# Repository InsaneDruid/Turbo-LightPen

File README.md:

# Turbo-LightPen
A 100% compatible replica of the Turbo Light Pen originally made for the C64. Can also work on the *High Speed Graphik* addon for the CBM PET line.

[Schematic](https://github.com/InsaneDruid/Turbo-LightPen/blob/main/Turbo-LightPen.pdf "Schematic")  

[Bill of Materials](https://htmlpreview.github.io/?https://github.com/InsaneDruid/Turbo-LightPen/blob/main/bom/Turbo-LightPen_bom.html "Bill of Materials")

## The License
This work is licensed under a Creative Commons Attribution-ShareAlike 4.0 International License.  
See https://creativecommons.org/licenses/by-sa/4.0/.

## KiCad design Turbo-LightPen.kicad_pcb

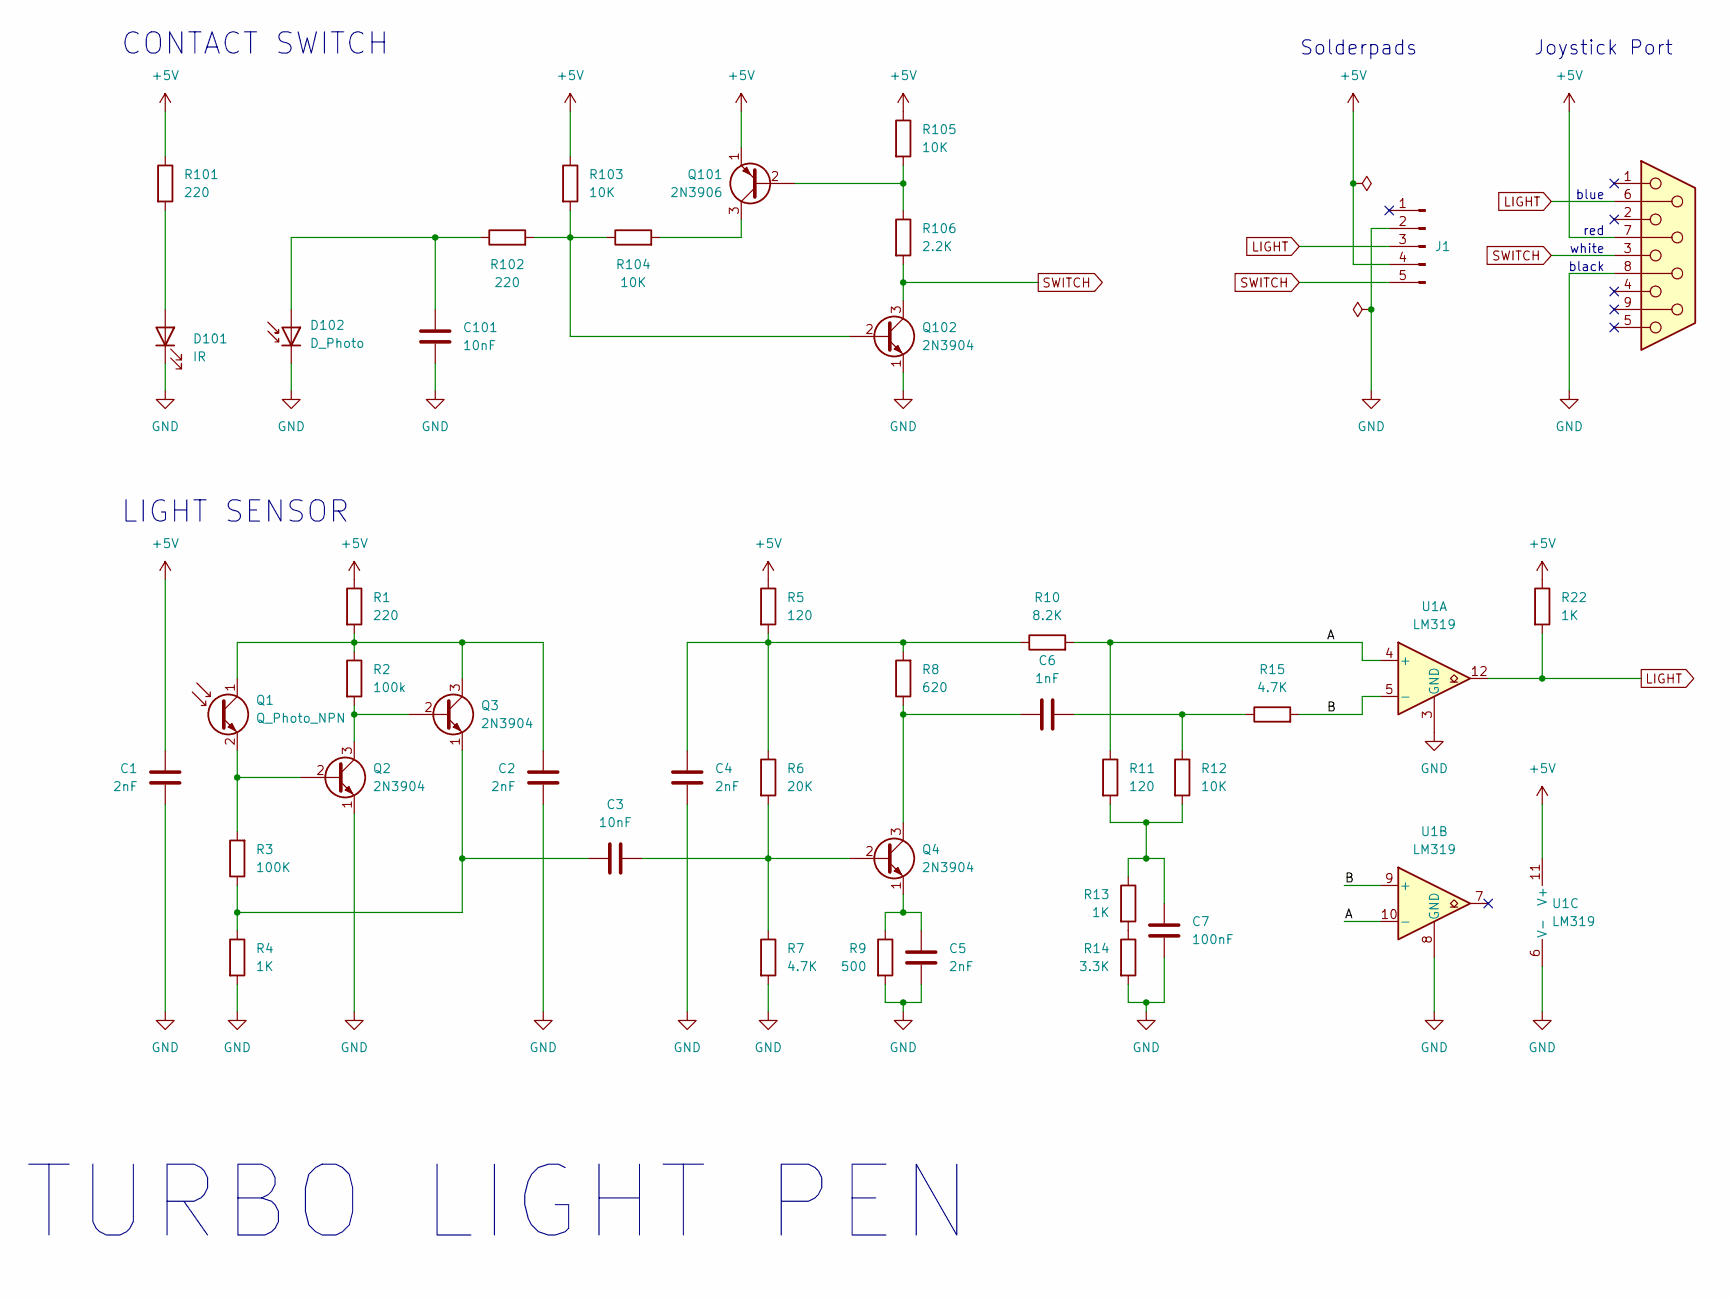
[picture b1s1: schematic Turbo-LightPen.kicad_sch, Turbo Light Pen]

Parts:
C1, C2, C4, C5: 2nF; C_Disc_D3.0mm_W1.6mm_P2.50mm
C3, C101: 10nF; C_Disc_D3.0mm_W1.6mm_P2.50mm
C6: 1nF; C_Disc_D3.0mm_W1.6mm_P2.50mm
C7: 100nF; C_Disc_D3.0mm_W1.6mm_P2.50mm
D101: IR; LED_Rectangular_W3.0mm_H2.0mm
D102: D_Photo; LED_Rectangular_W3.0mm_H2.0mm
J1: Conn_01x05_Pin; Cablepad_01x05
J2: Joystick Cable
Q1: Q_Photo_NPN; LED_D5.0mm_Horizontal_O6.35mm_Z3.0mm
Q2, Q3, Q4, Q102: 2N3904; TO-92_Inline
Q101: 2N3906; TO-92_Inline
R1, R101, R102: 220; R_Axial_DIN0204_L3.6mm_D1.6mm_P7.62mm_Horizontal
R2: 100k; R_Axial_DIN0204_L3.6mm_D1.6mm_P7.62mm_Horizontal
R3: 100K; R_Axial_DIN0204_L3.6mm_D1.6mm_P7.62mm_Horizontal
R4, R13, R22: 1K; R_Axial_DIN0204_L3.6mm_D1.6mm_P7.62mm_Horizontal
R5, R11: 120; R_Axial_DIN0204_L3.6mm_D1.6mm_P7.62mm_Horizontal
R6: 20K; R_Axial_DIN0204_L3.6mm_D1.6mm_P7.62mm_Horizontal
R7, R15: 4.7K; R_Axial_DIN0204_L3.6mm_D1.6mm_P7.62mm_Horizontal
R8: 620; R_Axial_DIN0204_L3.6mm_D1.6mm_P7.62mm_Horizontal
R9: 500; R_Axial_DIN0204_L3.6mm_D1.6mm_P7.62mm_Horizontal
R10: 8.2K; R_Axial_DIN0204_L3.6mm_D1.6mm_P7.62mm_Horizontal
R12, R103, R104, R105: 10K; R_Axial_DIN0204_L3.6mm_D1.6mm_P7.62mm_Horizontal
R14: 3.3K; R_Axial_DIN0204_L3.6mm_D1.6mm_P7.62mm_Horizontal
R106: 2.2K; R_Axial_DIN0204_L3.6mm_D1.6mm_P7.62mm_Horizontal
U1: LM319; DIP-14_W7.62mm

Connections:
+5V: C1.2, J1.4, J2.7, Q101.1 (E), R1.1, R5.1, R22.1, R101.1, R103.1, R105.1, U1.11 (V+)
/A: R10.2, R11.1, U1.4 (+), U1.10 (-)
/B: R15.2, U1.5 (-), U1.9 (+)
GND: C1.1, C2.1, C4.1, C5.2, C7.2, C101.2, D101.1 (K), D102.1 (K), J1.2, J2.8, Q2.1 (E), Q102.1 (E), R4.2, R7.2, R9.2, R14.2, U1.3 (GND), U1.6 (V-), U1.8 (GND)
LIGHT: J1.3, J2.6, R22.2, U1.12
unnamed: C4.2, R5.2, R6.1, R8.2, R10.1
unnamed: C6.2, R12.1, R15.1
unnamed: C7.1, R11.2, R12.2, R13.1
unnamed: D101.2 (A), R101.2
unnamed: C101.1, D102.2 (A), R102.1
unnamed: C2.2, Q1.1 (C), Q3.3 (C), R1.2, R2.1
unnamed: Q1.2 (E), Q2.2 (B), R3.2
unnamed: Q2.3 (C), Q3.2 (B), R2.2
unnamed: C3.1, Q3.1 (E), R3.1, R4.1
unnamed: C3.2, Q4.2 (B), R6.2, R7.1
unnamed: C6.1, Q4.3 (C), R8.1
unnamed: C5.1, Q4.1 (E), R9.1
unnamed: Q101.2 (B), R105.2, R106.1
unnamed: Q101.3 (C), R104.2
unnamed: Q102.2 (B), R102.2, R103.2, R104.1
unnamed: R13.2, R14.1
SWITCH: J1.5, J2.3, Q102.3 (C), R106.2

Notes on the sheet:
black
Joystick Port
TURBO LIGHT PEN
white
red
blue
CONTACT SWITCH
LIGHT SENSOR
Solderpads

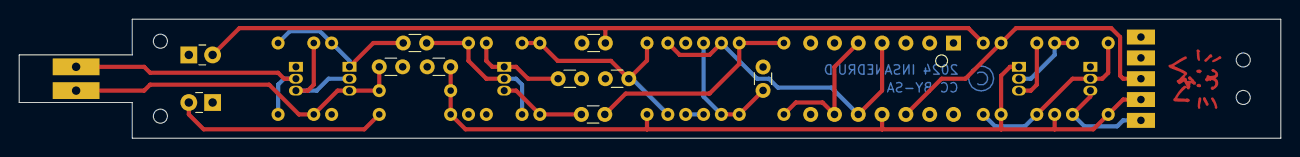
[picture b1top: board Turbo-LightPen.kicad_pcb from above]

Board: 2 copper layers, 134.6 x 12.7 mm, 42 parts (0 on the bottom side), 22 nets.

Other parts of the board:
mounting_front: turbo-lightpen_mountingholes_front
mounting_rear: turbo-lightpen_mountingholes_rear

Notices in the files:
Turbo-LightPen.kicad_pcb:
License: CC BY-SA 4.0
CC BY-SA
